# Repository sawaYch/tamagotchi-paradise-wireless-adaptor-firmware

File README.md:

# Tamagotchi Paradise Wireless Adaptor

A Bluetooth transparent serial bridge for **Tamagotchi Paradise**. It lets PC and mobile tools such as [**TamaHome**](https://bbamorachi.us/tamahome-toolkit-windows/), [**BBSite**](https://tools.bbamorachi.us/), [**Paramix Studio**](https://mameise.github.io/Paramix-Studio/), and similar UART-based apps talk to the device wirelessly over Bluetooth instead of a wired USB–UART cable.

Built around an **ESP32-WROOM-32E-N4** module, the adaptor sits between the host and Tamagotchi Paradise and forwards bytes in both directions at 460800 baud.

## Rev 1.0

_The silk print on the back TX RX means connect to TMGC's TX RX. It is not TX RX of the ESP32. Wireless adaptor case rev 1.0 still in early prototyping phase._

## Why this exists

Official and community tools expect a serial (UART / Web Serial) connection. That works well on desktop with a cable, but:

- Many platforms only expose Bluetooth reliably (especially mobile)
- Some browsers have Web Bluetooth but not Web Serial
- A small wireless bridge is easier to leave connected to the Tamagotchi

This project provides the hardware, firmware, and (for web tools) a BLE Web Serial shim so the same tools can work across **Windows, macOS, Linux, Android, and iOS**.

## How it works

```text
Host app (TamaHome / BBSite / …)
        │
        │  Bluetooth Classic SPP  or  BLE
        ▼
   ESP32-WROOM-32E-N4 bridge board
        │
        │  UART @ 460800 (GPIO16 RX / GPIO17 TX)
        ▼
  Tamagotchi Paradise
```

A mode switch on the board selects the radio link:

| Mode                               | Switch            | Typical use                          |
| ---------------------------------- | ----------------- | ------------------------------------ |
| **SPP** (Classic Bluetooth serial) | SW open           | Desktop apps, Chrome, Android Chrome |
| **BLE**                            | SW shorted to GND | BLE only for iOS Bluefy BBSite       |

Device names:

- SPP: `Tamagotchi Paradise Bridge SPP`
- BLE: `Tamagotchi Paradise Bridge`

## Repository layout

| Path                                                                         | Contents                                                                          |
| ---------------------------------------------------------------------------- | --------------------------------------------------------------------------------- |
| [`firmware/tama_bridge/`](firmware/tama_bridge/)                             | Arduino / ESP32 firmware (SPP + BLE bridge)                                       |
| [`hardware/esp32-wroom-32e-n4-single/`](hardware/esp32-wroom-32e-n4-single/) | KiCad project for the ESP32-WROOM-32E-N4 board, plus Gerbers, BOM, and CPL        |
| [`hardware/README.md`](hardware/README.md)                                   | Pad map, flashing, and fabrication notes                                          |
| [`worker/`](worker/)                                                         | Cloudflare Worker that proxies web tools and injects a BLE Web Serial shim        |
| [`tools/ble-loopback/`](tools/ble-loopback/)                                 | Optional local BLE throughput / shim test pages (dev tools for protocol analysis) |
| [`tools/TamaHomeLaunch/`](tools/TamaHomeLaunch/)                             | Windows launcher so stock TamaHome can open the Bluetooth COM port at 460800      |

The adaptor also needs a case and a rechargeable LiPo battery circuit. See https://github.com/sawaYch/tamagotchi-paradise-uart-adaptor/tree/main/models/wireless

## Firmware

Sketch: [`firmware/tama_bridge/tama_bridge.ino`](firmware/tama_bridge/tama_bridge.ino)

- Arduino board: **ESP32 Dev Module** (4 MB flash is enough)
- Pins: UART2 on **IO16** (RX from Tamagotchi), **IO17** (TX to Tamagotchi); mode on **IO4**. Firmware also drives **IO2**, which this board does not bring out to a pad or LED.
- Build options in `build_opt.h` raise NimBLE buffers / MTU for better BLE throughput

Flash over the board’s USB-C port (onboard CH340X): hold **BOOT**, press **RST**, release **BOOT**, then upload. See [`hardware/README.md`](hardware/README.md).

## Hardware

One board, [`hardware/esp32-wroom-32e-n4-single/`](hardware/esp32-wroom-32e-n4-single/): a 2-layer, 20.0 × 31.35 mm PCB (1.6 mm, 1 oz). The ESP32-WROOM-32E-N4 antenna extends about 6.25 mm past the board edge. The module runs from an external 3.3 V LiPo regulator through an LM66100 ideal diode. USB-C powers a CH340X for programming and does not feed the battery rail.

Hand-solder pads on the back edge:

- GPIO16 / GPIO17 — Tamagotchi UART at 460800 baud
- GPIO4 — mode switch to GND
- BAT+ / BAT− — 3.3 V from the external battery module

Pad map, BOM, and Gerbers: [`hardware/README.md`](hardware/README.md).

## Web tools (BLE shim)

Desktop Web Serial apps usually need Classic serial or SPP. On platforms where only BLE is available, [`worker/`](worker/) runs a Cloudflare Worker that:

1. Proxies the upstream tools site
2. Injects [`worker/public/__tama/shim.js`](worker/public/__tama/shim.js), which implements `navigator.serial` on top of Web Bluetooth NUS

That lets browser-based tools reuse their existing Web Serial code path over BLE.

## Platform notes

| Platform | Typical path                             | Application                                                                                                           |
| -------- | ---------------------------------------- | --------------------------------------------------------------------------------------------------------------------- |
| Windows  | SPP                                      | TamaHome through [TamaHomeLaunch](#windows-tamahome-tamahomelaunch) ✅ <br/> bbamorachi.us ✅ <br/> Paramix Studio ✅ |
| MacOS    | SPP                                      | TamaHome ✅ <br/> bbamorachi.us ✅ <br/> Paramix Studio ✅                                                            |
| Linux    | SPP                                        | \*untested                                                                                                            |
| Android  | SPP via Chrome in Desktop site mode      | bbamorachi.us ✅ <br/> Paramix Studio ✅                                                                              |
| iOS      | BLE via Bluefy web browser | bbamorachi.us ✅ <br/> Paramix Studio ✅                                                                              |

Exact app support depends on each tool (TamaHome, BBSite, etc.). The adaptor only provides a transparent UART bridge.

## Windows TamaHome (TamaHomeLaunch)

Stock TamaHome on Windows cannot open this adaptor's Bluetooth serial port. [`tools/TamaHomeLaunch`](tools/TamaHomeLaunch) starts TamaHome and skips that one check in memory. It does not edit TamaHome's files. Browser tools such as BBSite do not need it: Chrome Web Serial does not have this check.

### Why it is needed

TamaHome talks to Tamagotchi Paradise at **460800** baud. This firmware keeps that rate on the UART between the ESP32 and the Tamagotchi (GPIO16 / GPIO17). Bluetooth SPP only carries the bytes. The baud number on the Windows COM port does not set the radio speed, and the Microsoft Bluetooth serial driver accepts `460800`.

The failure happens before the driver is asked. Windows reports the Bluetooth COM port's maximum baud as **115200**. TamaHome uses .NET `System.IO.Ports`, which reads that maximum and throws:

```text
The maximum baud rate for the device is 115200 (Parameter 'baudRate')
```

A wired CP2102, CH340, or FTDI port reports a maximum high enough for 460800, so the same TamaHome build works on a USB–UART cable and stops on Bluetooth.

Editing `System.IO.Ports.dll` inside the TamaHome folder removes the check, but a TamaHome update replaces that file. The launcher leaves the install untouched. Each time it starts TamaHome, it loads a small startup hook (`TamaHomeBaudHook.dll`) that skips the maximum-baud test in that process only.

### Build

TamaHome already requires the .NET 8 desktop runtime. From this repository:

```text
dotnet publish tools/TamaHomeLaunch/TamaHomeLaunch.csproj -c Release
```

The program is:

```text
tools/TamaHomeLaunch/bin/Release/net8.0/publish/TamaHomeLaunch.exe
```

`TamaHomeBaudHook.dll` is written next to that exe. Keep those files together. Point a shortcut at `TamaHomeLaunch.exe`, not at `TamaParadiseTool.exe`.

### Use

1. Pair **Tamagotchi Paradise Bridge SPP** in Windows. Leave the adaptor's mode switch open (SPP). Shorting the switch to GND selects BLE, which TamaHome does not use.
2. Start **TamaHomeLaunch.exe**. It runs `E:\TamaParadiseTool\TamaParadiseTool.exe`. If TamaHome is installed somewhere else, pass that path:

   ```text
   TamaHomeLaunch.exe "D:\Apps\TamaParadiseTool\TamaParadiseTool.exe"
   ```

3. In TamaHome, connect to the **Outgoing** Bluetooth COM port.

Windows creates two ports, both often named "Standard Serial over Bluetooth link". Only the Outgoing port connects to the adaptor. The Incoming port is for a remote device calling this PC. This adaptor is the server, so it never calls in. The Incoming port still opens, then every write waits until it times out. Cancelling that wait can freeze TamaHome. In Device Manager, the Outgoing port's device id contains the adaptor's Bluetooth address. The Incoming port's address is all zeros.

If the launcher cannot find TamaHome or the hook DLL, it shows a message box. A startup log is appended to `%LocalAppData%\TamaHomeLaunch\hook.log`. A normal start records that two baud checks were skipped.

## Extra Setup on iOS

Since iOS only support BLE, it does not create a serial COM port in web browser like Chrome. You need to install Bluefy (free on iOS App Store):

- https://bluefy.app/
- https://apps.apple.com/us/app/bluefy-web-ble-browser/id1492822055

### Highly suggest you to create a iOS ShortCut to visit the proxied Tamagotchi Web Tools:

1. Open "Shortcuts"  

2. Click "All Shortcuts"  

3. Click "+" sign to add new shortcut  

4. Select "Open URL" (Not Open App)  

5. Fill-in url "bluefy://{your hosted proxy website for tmgc web tools}"

6. Done. Now you click the newly added shortcut on Home Screen should open Bluefy with TMGC Web Tools. Toggle the wireless adaptor to BLE mode, and the on the web tools click "Connect USB", you should see the BLE adaptor device. Connect to it, then plug the wireless adaptor to your Tamagotchi Paradise, you should be able to transfer Gift, Lab items, etc.

## License

This project is licensed under the [MIT License](LICENSE).

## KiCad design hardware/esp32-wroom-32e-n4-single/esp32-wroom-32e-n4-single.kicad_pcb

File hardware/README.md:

# Hardware

The adaptor is one board: [`esp32-wroom-32e-n4-single`](esp32-wroom-32e-n4-single/).

Open [`esp32-wroom-32e-n4-single.kicad_pro`](esp32-wroom-32e-n4-single/esp32-wroom-32e-n4-single.kicad_pro) in KiCad.

## Board

| | |
| --- | --- |
| Module | ESP32-WROOM-32E-N4 |
| Layers | 2 |
| Copper | 1 oz |
| Thickness | 1.6 mm |
| Outline | 20.0 × 31.35 mm |
| Fabrication | JLCPCB |

The board edge runs from y = 6.25 mm to y = 37.6 mm. The module antenna sits in the 6.25 mm outside that edge, so the assembled length is about 37.6 mm.

USB-C (HRO TYPE-C-31-M-12) is a device (sink). VBUS powers the CH340X only. The ESP32 runs from BAT+ through an LM66100 ideal diode. BAT+ is 3.3 V from an external LiPo module, so USB and the battery can be connected at the same time without tying VBUS to the battery rail.

## Hand-solder pads

The pads are 1.0 mm and sit on the back edge. Left to right below is KiCad’s coordinate order, with x = 0 at the GPIO16 end. Back silkscreen reads **TX, RX, GND, SW, −, +**. Those silk names are the external wire: TX is the Tamagotchi TX line, which is the ESP32 RX pin.

| Silk | Ref | Net | Connect |
| --- | --- | --- | --- |
| TX | TP4 | GPIO16 | Tamagotchi UART TX (ESP32 RX) |
| RX | TP5 | GPIO17 | Tamagotchi UART RX (ESP32 TX) |
| GND | TP6 | GND | Tamagotchi ground |
| SW | TP3 | GPIO4 | Mode switch to GND. Open = SPP, shorted = BLE |
| − | TP2 | GND | Battery return (BAT−) |
| + | TP1 | BAT+ | 3.3 V from the external LiPo module |

UART is 460800 baud.

SW1 is RESET (EN). SW2 is BOOT (IO0).

## Flashing

Plug in USB-C. The CH340X shows up as a USB–UART. In Arduino, select **ESP32 Dev Module**. 4 MB flash is enough.

1. Hold **BOOT** (SW2).
2. Press and release **RESET** (SW1).
3. Release **BOOT**.
4. Upload [`firmware/tama_bridge/tama_bridge.ino`](../firmware/tama_bridge/tama_bridge.ino).

R9 (4.7 kΩ) between CH340X pins 5 and 6 selects push-pull DTR, idle high, for the auto-reset pair Q1 and Q2.

The firmware also drives GPIO2. This board does not bring GPIO2 out to a pad or an LED.

## Fabrication files

All order files are in [`esp32-wroom-32e-n4-single/fab/`](esp32-wroom-32e-n4-single/fab/).

| File | Use |
| --- | --- |
| `esp32-wroom-32e-n4-single-gerbers.zip` | Gerbers and drills for JLCPCB |
| `gerbers/` | The same plot, unpacked |
| `jlc_bom.csv` | JLCPCB assembly BOM |
| `jlc_cpl.csv` | JLCPCB pick-and-place |
| `bom-kicad.csv` | KiCad BOM export |
| `pos-raw.csv`, `esp32-wroom-32e-n4-single-all-pos.csv` | Position exports |

U1 (ESP32-WROOM-32E-N4) and U2 (CH340X) have no LCSC number in `jlc_bom.csv`. Fill those in before ordering assembly. The USB-C datasheet is [`datasheets/TYPE-C-31-M-12.pdf`](esp32-wroom-32e-n4-single/datasheets/TYPE-C-31-M-12.pdf).

## BOM

| Ref | Value | MPN | Notes |
| --- | --- | --- | --- |
| U1 | ESP32-WROOM-32E-N4 | ESP32-WROOM-32E-N4 | LCSC number not filled |
| U2 | CH340X | CH340X | USB–UART, powered from VBUS. LCSC number not filled |
| U3 | LM66100DCK | LM66100DCKT | BAT+ to +3V3 ideal diode. LCSC C2832141 |
| J1 | USB-C | TYPE-C-31-M-12 | HRO. LCSC C165948 |
| SW1, SW2 | Tactile | B3U-1000P | RESET and BOOT. LCSC C231329 |
| Q1, Q2 | 2N7002 | 2N7002 | Auto-reset and auto-boot |
| R1, R2 | 5.1 kΩ | 0402WGF5101TCE | USB CC sink resistors |
| R3–R6 | 10 kΩ | 0402WGF1002TCE | EN, IO0, and MOSFET gates |
| R7, R8 | 470 Ω | RC0402FR-07470RL | UART series resistors |
| R9 | 4.7 kΩ | 0402WGF4701TCE | CH340X DTR mode |
| C1 | 10 µF | CL05A106MQ5NUNC | +3V3 bulk |
| C2–C5 | 100 nF | CL05B104KO5NNNC | Bypass |

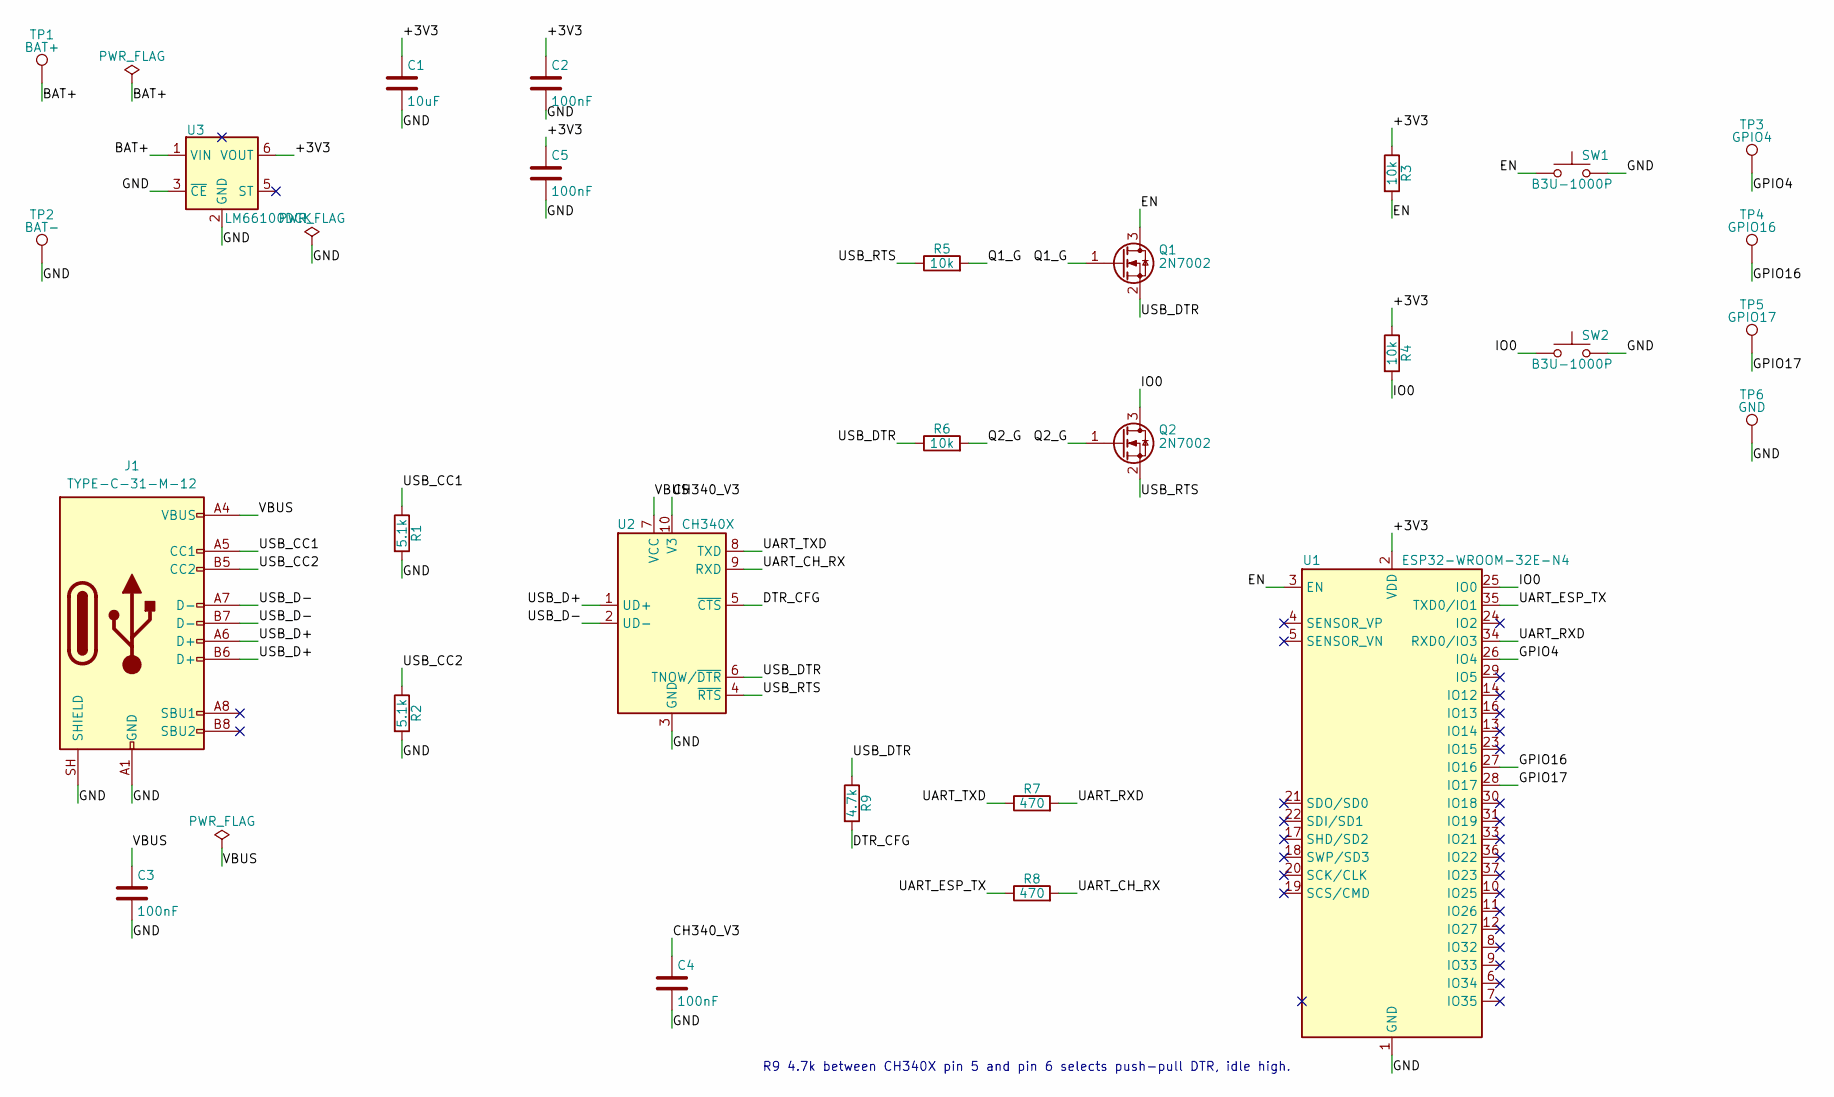
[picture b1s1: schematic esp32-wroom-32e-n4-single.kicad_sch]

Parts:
C1: 10uF; C_0402_1005Metric
C2, C3, C4, C5: 100nF; C_0402_1005Metric
J1: TYPE-C-31-M-12; USB_C_Receptacle_HRO_TYPE-C-31-M-12
Q1, Q2: 2N7002; SOT-23
R1, R2: 5.1k; R_0402_1005Metric
R3, R4, R5, R6: 10k; R_0402_1005Metric
R7, R8: 470; R_0402_1005Metric
R9: 4.7k; R_0402_1005Metric
SW1, SW2: B3U-1000P; SW_SPST_B3U-1000P
TP1: BAT+; TestPoint_Pad_D1.0mm
TP2: BAT-; TestPoint_Pad_D1.0mm
TP3: GPIO4; TestPoint_Pad_D1.0mm
TP4: GPIO16; TestPoint_Pad_D1.0mm
TP5: GPIO17; TestPoint_Pad_D1.0mm
TP6: GND; TestPoint_Pad_D1.0mm
U1: ESP32-WROOM-32E-N4; ESP32-WROOM-32E
U2: CH340X; MSOP-10_3x3mm_P0.5mm
U3: LM66100DCK; SOT-363_SC-70-6

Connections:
/+3V3: C1.1, C2.1, C5.1, R3.1, R4.1, U1.2 (VDD), U3.6 (VOUT)
/BAT+: TP1.1, U3.1 (VIN)
/CH340_V3: C4.1, U2.10 (V3)
/DTR_CFG: R9.2, U2.5 (~CTS)
/EN: Q1.3 (D), R3.2, SW1.1, U1.3 (EN)
/GND: C1.2, C2.2, C3.2, C4.2, C5.2, J1.A1 (GND), J1.A12 (GND), J1.B1 (GND), J1.B12 (GND), J1.SH (SHIELD), R1.2, R2.2, SW1.2, SW2.2, TP2.1, TP6.1, U1.1 (GND), U1.15 (GND), U1.38 (GND), U1.39 (GND), U2.3 (GND), U3.2 (GND), U3.3 (~CE)
/GPIO4: TP3.1, U1.26 (IO4)
/GPIO16: TP4.1, U1.27 (IO16)
/GPIO17: TP5.1, U1.28 (IO17)
/IO0: Q2.3 (D), R4.2, SW2.1, U1.25 (IO0)
/Q1_G: Q1.1 (G), R5.2
/Q2_G: Q2.1 (G), R6.2
/UART_CH_RX: R8.2, U2.9 (RXD)
/UART_ESP_TX: R8.1, U1.35 (TXD0/IO1)
/UART_RXD: R7.2, U1.34 (RXD0/IO3)
/UART_TXD: R7.1, U2.8 (TXD)
/USB_CC1: J1.A5 (CC1), R1.1
/USB_CC2: J1.B5 (CC2), R2.1
/USB_D+: J1.A6 (D+), J1.B6 (D+), U2.1 (UD+)
/USB_D-: J1.A7 (D-), J1.B7 (D-), U2.2 (UD-)
/USB_DTR: Q1.2 (S), R6.1, R9.1, U2.6 (TNOW/~DTR)
/USB_RTS: Q2.2 (S), R5.1, U2.4 (~RTS)
/VBUS: C3.1, J1.A4 (VBUS), J1.A9 (VBUS), J1.B4 (VBUS), J1.B9 (VBUS), U2.7 (VCC)

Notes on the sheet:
R9 4.7k between CH340X pin 5 and pin 6 selects push-pull DTR, idle high.

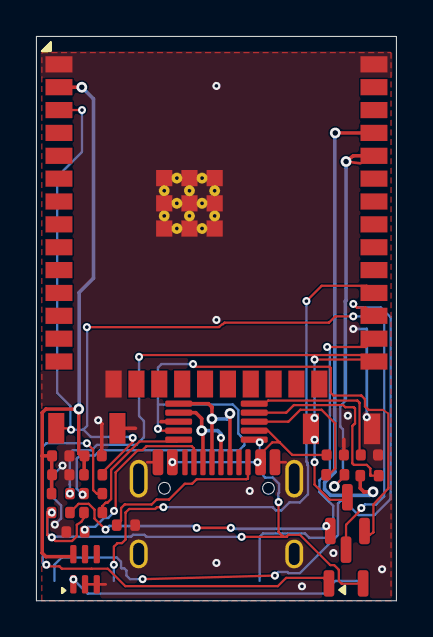
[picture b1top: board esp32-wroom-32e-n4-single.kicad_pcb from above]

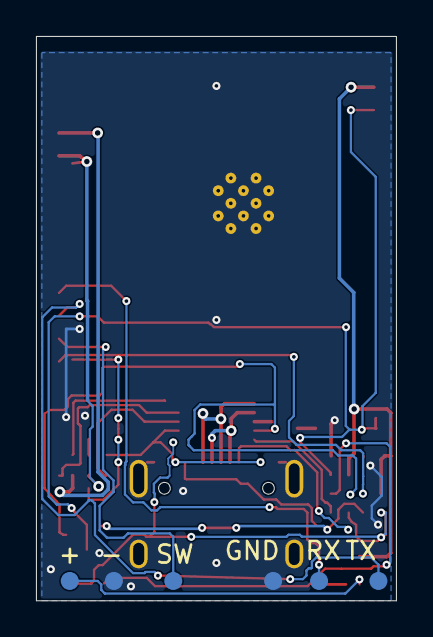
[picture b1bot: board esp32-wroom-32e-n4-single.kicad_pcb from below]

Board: 2 copper layers, 20.0 x 31.4 mm, 28 parts (6 on the bottom side), 23 nets.

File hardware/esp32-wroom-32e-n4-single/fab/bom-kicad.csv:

"Reference","Value","Footprint","QUANTITY"
"C1","10uF","Capacitor_SMD:C_0402_1005Metric","1"
"C2-C5","100nF","Capacitor_SMD:C_0402_1005Metric","4"
"J1","TYPE-C-31-M-12","Connector_USB:USB_C_Receptacle_HRO_TYPE-C-31-M-12","1"
"Q1,Q2","2N7002","Package_TO_SOT_SMD:SOT-23","2"
"R1,R2","5.1k","Resistor_SMD:R_0402_1005Metric","2"
"R3-R6","10k","Resistor_SMD:R_0402_1005Metric","4"
"R7,R8","470","Resistor_SMD:R_0402_1005Metric","2"
"R9","4.7k","Resistor_SMD:R_0402_1005Metric","1"
"SW1,SW2","B3U-1000P","Button_Switch_SMD:SW_SPST_B3U-1000P","2"
"TP1","BAT+","TestPoint:TestPoint_Pad_D1.0mm","1"
"TP2","BAT-","TestPoint:TestPoint_Pad_D1.0mm","1"
"TP3","GPIO4","TestPoint:TestPoint_Pad_D1.0mm","1"
"TP4","GPIO16","TestPoint:TestPoint_Pad_D1.0mm","1"
"TP5","GPIO17","TestPoint:TestPoint_Pad_D1.0mm","1"
"TP6","GND","TestPoint:TestPoint_Pad_D1.0mm","1"
"U1","ESP32-WROOM-32E-N4","RF_Module:ESP32-WROOM-32E","1"
"U2","CH340X","Package_SO:MSOP-10_3x3mm_P0.5mm","1"
"U3","LM66100DCK","Package_TO_SOT_SMD:SOT-363_SC-70-6","1"

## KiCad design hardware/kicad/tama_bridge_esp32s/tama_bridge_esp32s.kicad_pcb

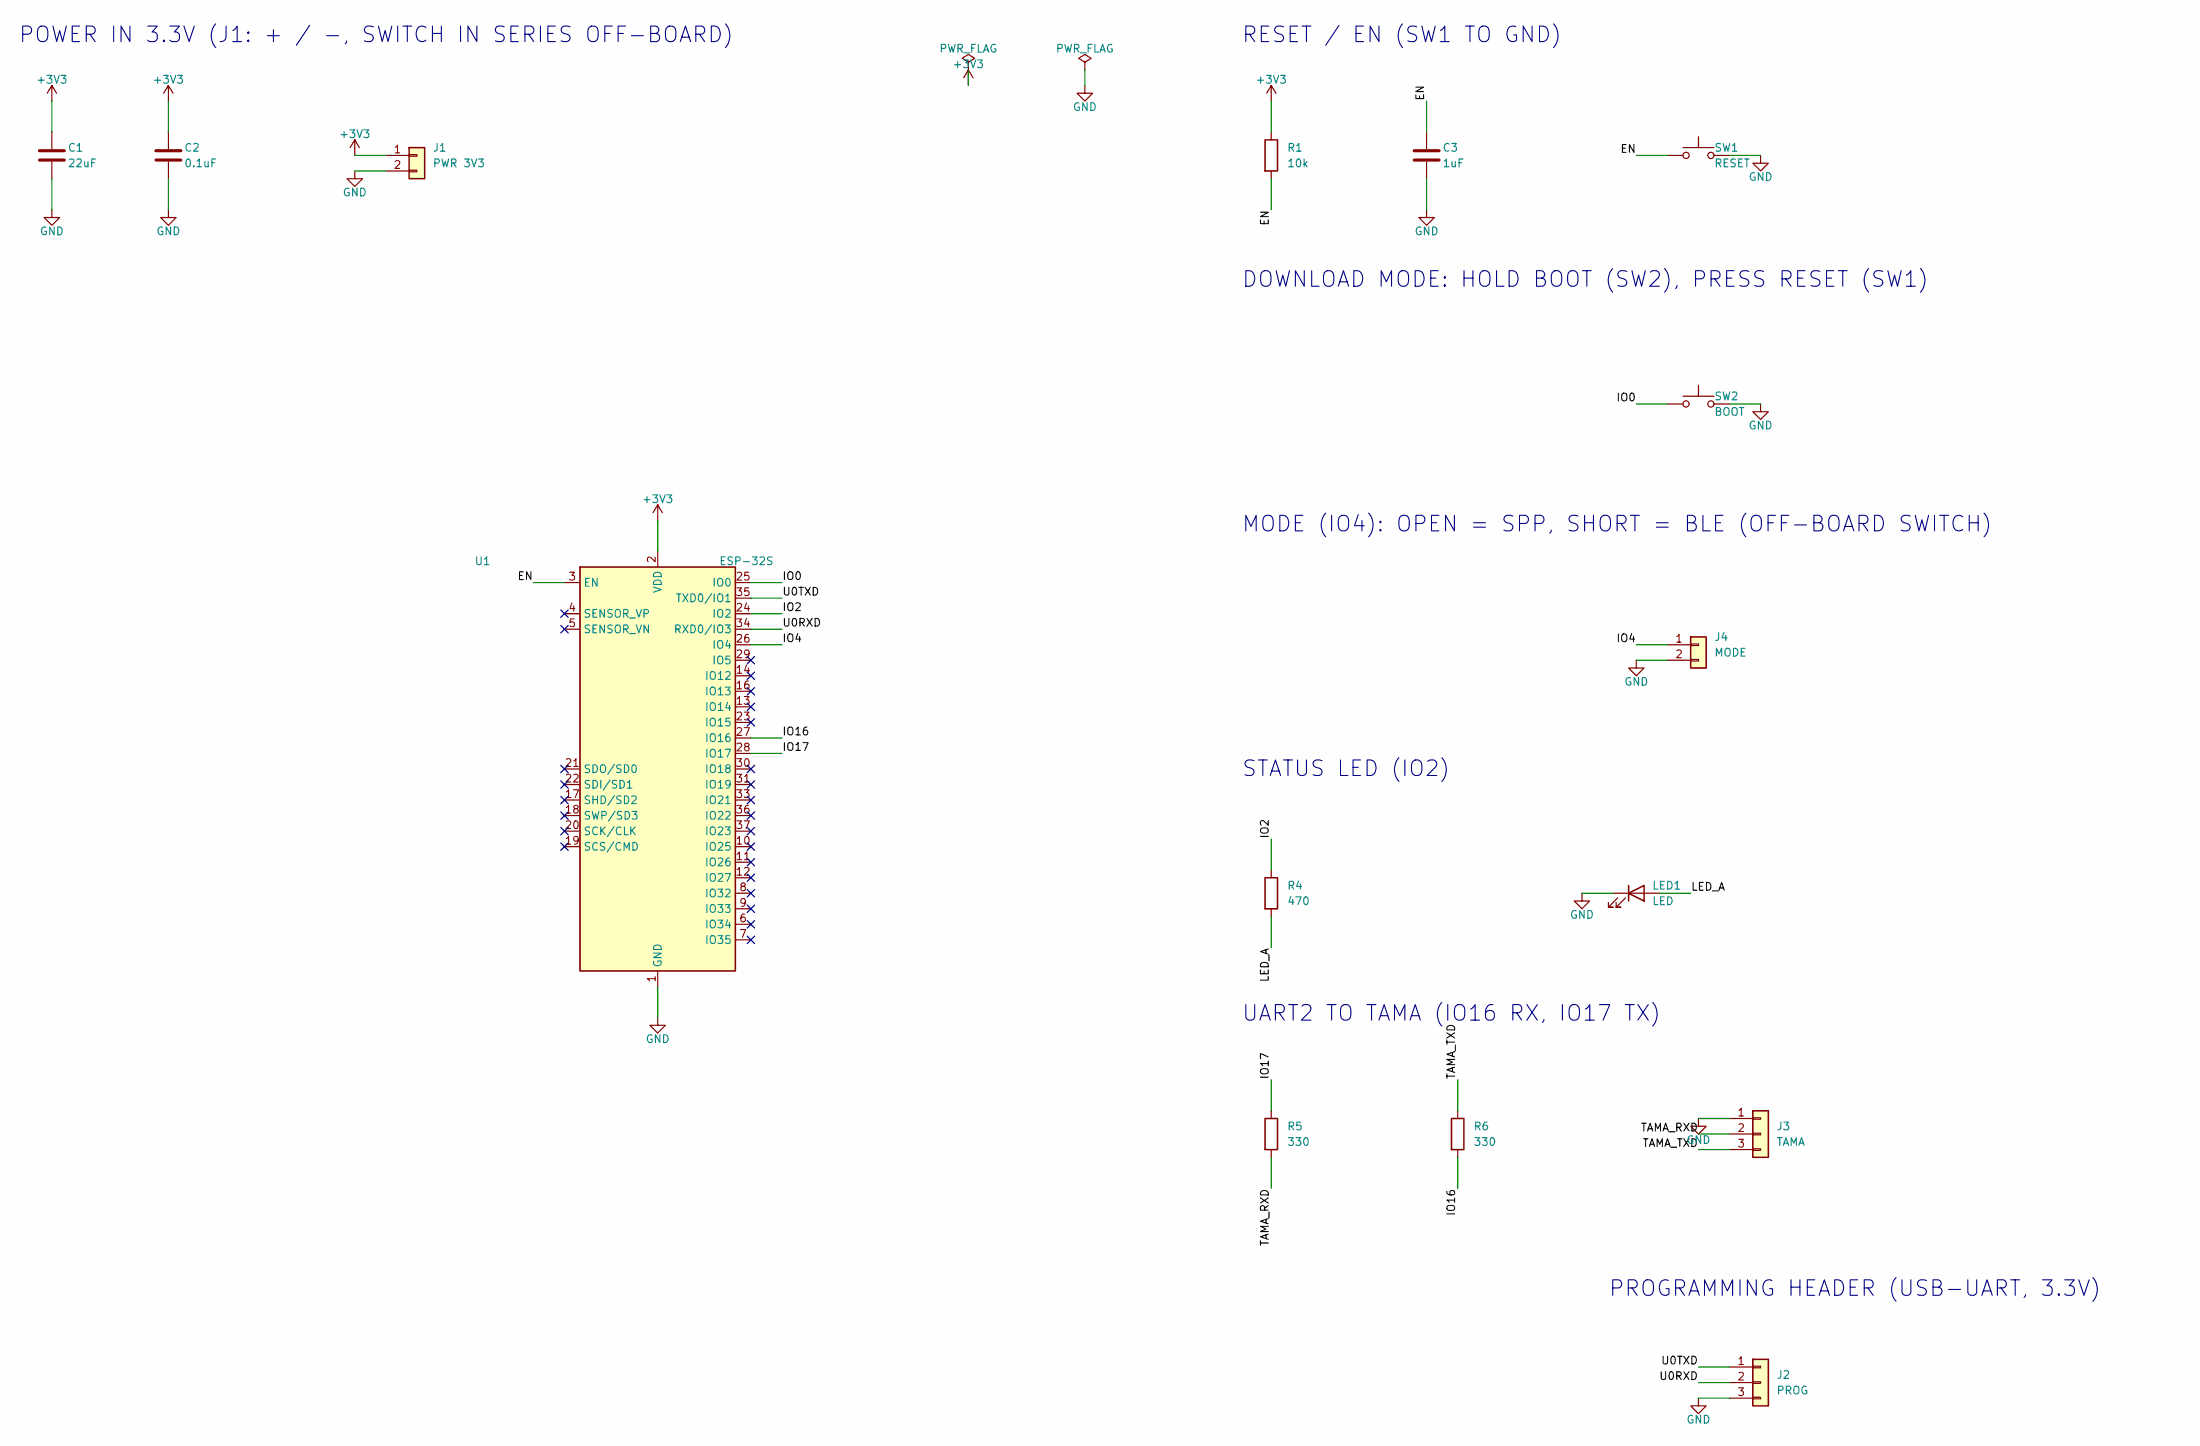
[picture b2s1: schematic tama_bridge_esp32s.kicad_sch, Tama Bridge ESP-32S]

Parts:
C1: 22uF; C_0805_2012Metric; LCSC C45783
C2: 0.1uF; C_0603_1608Metric; LCSC C1591
C3: 1uF; C_0603_1608Metric; LCSC C15849
J1: PWR 3V3; WirePads_1x02_P1.85mm
J2: PROG; WirePads_1x03_P1.85mm
J3: TAMA; WirePads_1x03_P1.85mm
J4: MODE; WirePads_1x02_P1.85mm
LED1: LED; LED_0603_1608Metric; LCSC C12624
R1: 10k; R_0603_1608Metric; LCSC C25804
R4: 470; R_0603_1608Metric; LCSC C23179
R5, R6: 330; R_0603_1608Metric; LCSC C23138
SW1: RESET; SW_SPST_TS-1088-xR025; LCSC C720477
SW2: BOOT; SW_SPST_TS-1088-xR025; LCSC C720477
U1: ESP-32S; ESP32-S; LCSC C277944

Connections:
+3V3: C1.1, C2.1, J1.1, R1.1, U1.2 (VDD)
/EN: C3.1, R1.2, SW1.1, U1.3 (EN)
/IO0: SW2.1, U1.25 (IO0)
/IO2: R4.1, U1.24 (IO2)
/IO4: J4.1, U1.26 (IO4)
/IO16: R6.2, U1.27 (IO16)
/IO17: R5.1, U1.28 (IO17)
/LED_A: LED1.2 (A), R4.2
/TAMA_RXD: J3.2, R5.2
/TAMA_TXD: J3.3, R6.1
/U0RXD: J2.2, U1.34 (RXD0/IO3)
/U0TXD: J2.1, U1.35 (TXD0/IO1)
GND: C1.2, C2.2, C3.2, J1.2, J2.3, J3.1, J4.2, LED1.1 (K), SW1.2, SW2.2, U1.1 (GND), U1.15 (GND), U1.38 (GND), U1.39 (GND)

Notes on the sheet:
POWER IN 3.3V (J1: + / -, SWITCH IN SERIES OFF-BOARD)
RESET / EN (SW1 TO GND)
DOWNLOAD MODE: HOLD BOOT (SW2), PRESS RESET (SW1)
MODE (IO4): OPEN = SPP, SHORT = BLE (OFF-BOARD SWITCH)
STATUS LED (IO2)
UART2 TO TAMA (IO16 RX, IO17 TX)
PROGRAMMING HEADER (USB-UART, 3.3V)

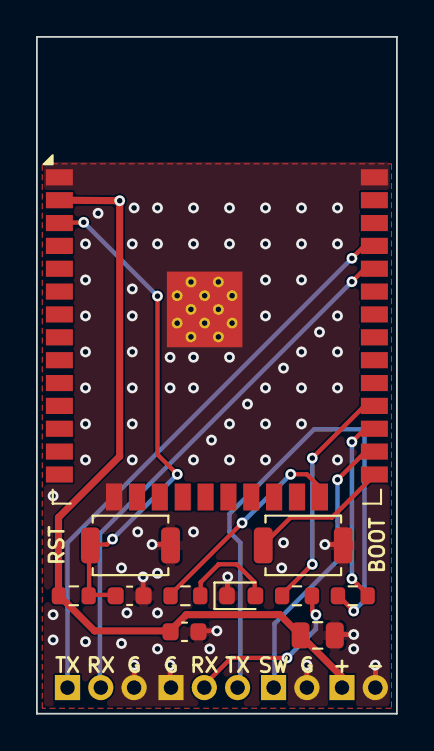
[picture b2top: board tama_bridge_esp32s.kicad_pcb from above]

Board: 2 copper layers, 20.0 x 37.6 mm, 15 parts (0 on the bottom side), 13 nets.

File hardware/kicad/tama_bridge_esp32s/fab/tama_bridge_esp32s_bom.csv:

Comment,Designator,Footprint,LCSC Part #
22uF,C1,C_0805_2012Metric,C45783
0.1uF,C2,C_0603_1608Metric,C1591
1uF,C3,C_0603_1608Metric,C15849
LED,LED1,LED_0603_1608Metric,C12624
10k,R1,R_0603_1608Metric,C25804
470,R4,R_0603_1608Metric,C23179
330,"R5,R6",R_0603_1608Metric,C23138
RESET,SW1,SW_SPST_TS-1088-xR025,C720477
BOOT,SW2,SW_SPST_TS-1088-xR025,C720477
ESP-32S,U1,ESP32-S,C277944
